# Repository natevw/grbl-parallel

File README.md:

# Grbl shield for CNC 3020/3040 parallel port

[work in progress]

This is an Eagle schematic and layout for connecting the Grbl's default pinout to the usual found on YooCNC-family "Chinese CNC" controller boxes. It is intended for isolation milling onto a single-layer PCB (using wires for the other layer).

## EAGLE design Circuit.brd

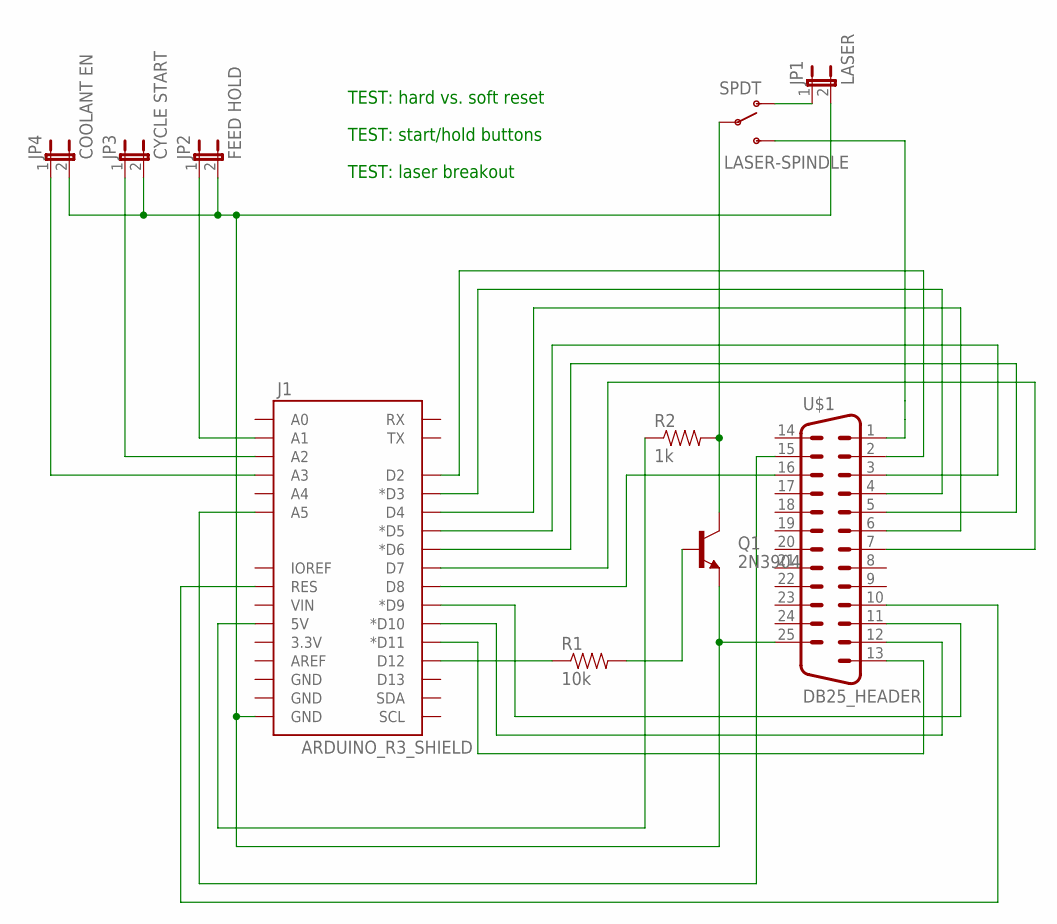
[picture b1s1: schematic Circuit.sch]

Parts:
J1: ARDUINO_R3_SHIELD; UNO_R3_SHIELD
JP1: LASER; 1X02
JP2: FEED HOLD; 1X02
JP3: CYCLE START; 1X02
JP4: COOLANT EN; 1X02
LASER-SPINDLE: SPDT; SWITCH-SPDT
Q1: 2N3904; TO-92-AMMO
R1: 10k; AXIAL-0.4
R2: 1k; AXIAL-0.4
U$1: DB25_HEADER

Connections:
unnamed: J1.RES, U$1.10
unnamed: J1.A5, U$1.15
unnamed: J1.D2, U$1.2
unnamed: J1.D3 (*D3), U$1.4
unnamed: J1.D4, U$1.6
unnamed: J1.D5 (*D5), U$1.3
unnamed: J1.D6 (*D6), U$1.5
unnamed: J1.D7, U$1.7
unnamed: J1.D8, U$1.16
unnamed: LASER-SPINDLE.2, Q1.1 (C), R2.P$2 (2)
unnamed: J1.D9 (*D9), U$1.11
unnamed: J1.D10 (*D10), U$1.12
unnamed: J1.D11 (*D11), U$1.13
unnamed: J1.A2, JP3.1
unnamed: Q1.2 (B), R1.P$2 (2)
unnamed: J1.D12, R1.P$1 (1)
unnamed: J1.5V, R2.P$1 (1)
unnamed: LASER-SPINDLE.3 (S), U$1.1
unnamed: J1.A1, JP2.1
unnamed: JP1.1, LASER-SPINDLE.1 (O)
unnamed: J1.GND@0 (GND), JP1.2, JP2.2, JP3.2, JP4.2, Q1.3 (E), U$1.25
unnamed: J1.A3, JP4.1

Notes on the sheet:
TEST: start/hold buttons
TEST: laser breakout
TEST: hard vs. soft reset

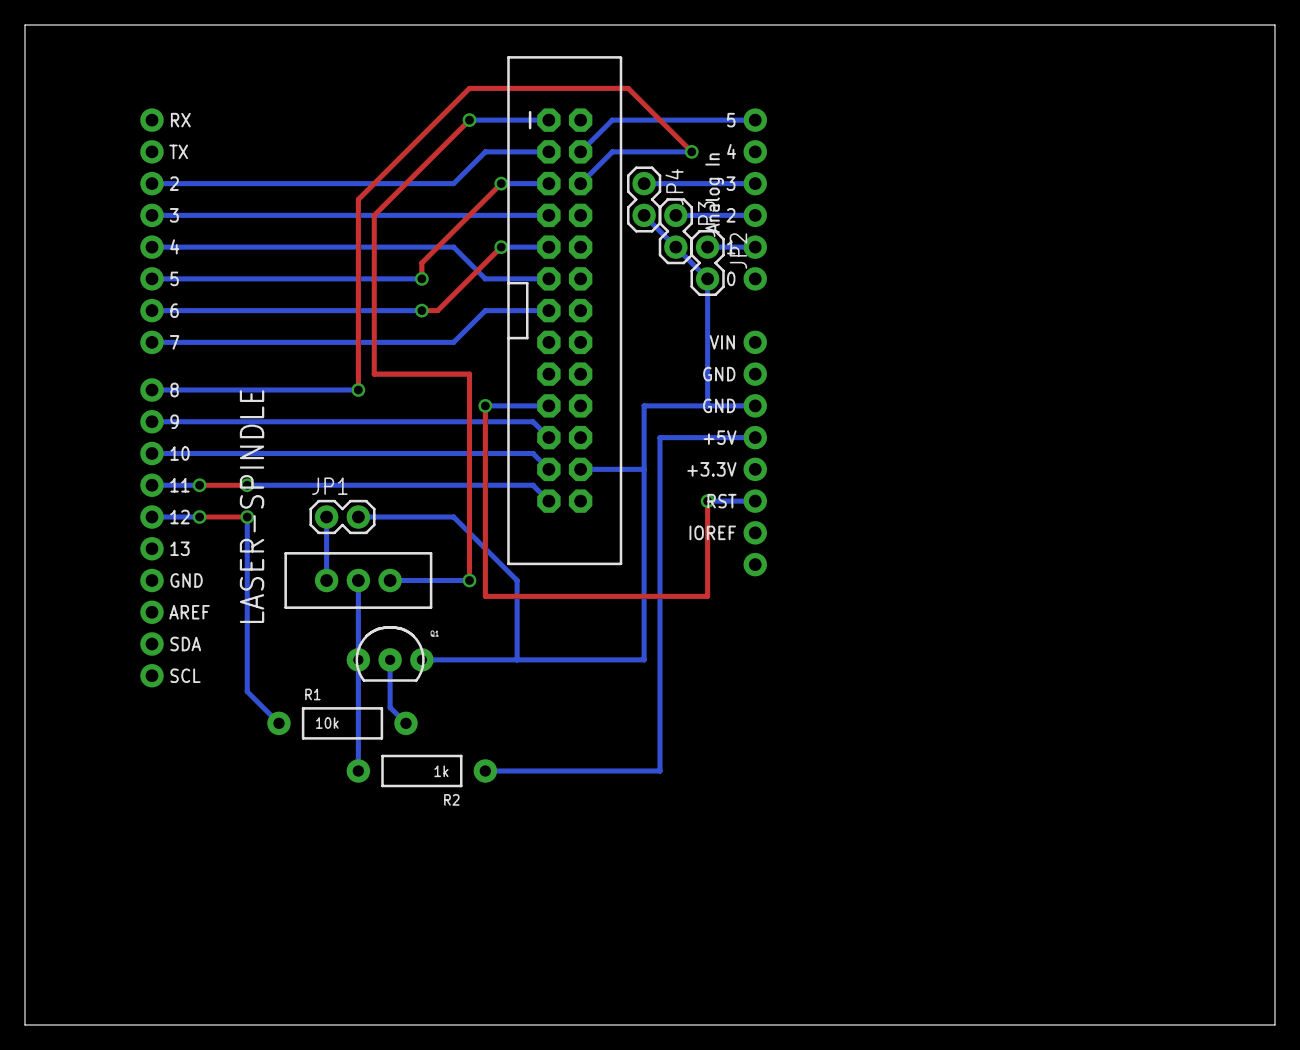
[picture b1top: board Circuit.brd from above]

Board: 2 copper layers, 100.0 x 80.0 mm, 10 parts (0 on the bottom side), 22 nets.

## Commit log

2015-03-03 version 1.0 (alpha) or something

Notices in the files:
parts and their libraries:
SparkFun-Boards: Licensing: Creative Commons ShareAlike 4.0 International - https://creativecommons.org/licenses/by-sa/4.0
